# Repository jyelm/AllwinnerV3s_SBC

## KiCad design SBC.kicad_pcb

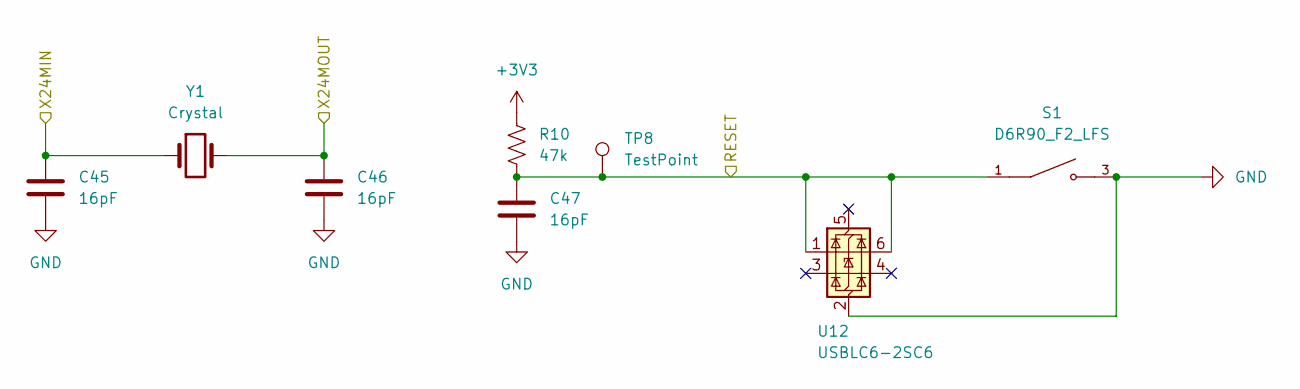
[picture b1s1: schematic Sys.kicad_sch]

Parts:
C45, C46, C47: 16pF; C_0603_1608Metric_Pad1.08x0.95mm_HandSolder
R10: 47k; R_0805_2012Metric_Pad1.20x1.40mm_HandSolder
S1: D6R90_F2_LFS; SW_D6R90_F2_LFS; PARTREV 21 Feb 22
TP8: TestPoint; TestPoint_Pad_D1.0mm
U12: USBLC6-2SC6; SOT-23-6
Y1: Crystal; Crystal_SMD_HC49-SD_HandSoldering

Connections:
+3V3: R10.1; also elsewhere on the board
/Allwinner V3S/RESET: C47.1, R10.2, S1.1, S1.2, TP8.1 (1_1), U12.1 (I/O1), U12.6 (I/O1); also elsewhere on the board
/Allwinner V3S/X24MIN: C45.1, Y1.1; also elsewhere on the board
/Allwinner V3S/X24MOUT: C46.1, Y1.2; also elsewhere on the board
GND: C45.2, C46.2, C47.2, S1.3, S1.4, U12.2 (GND); also elsewhere on the board

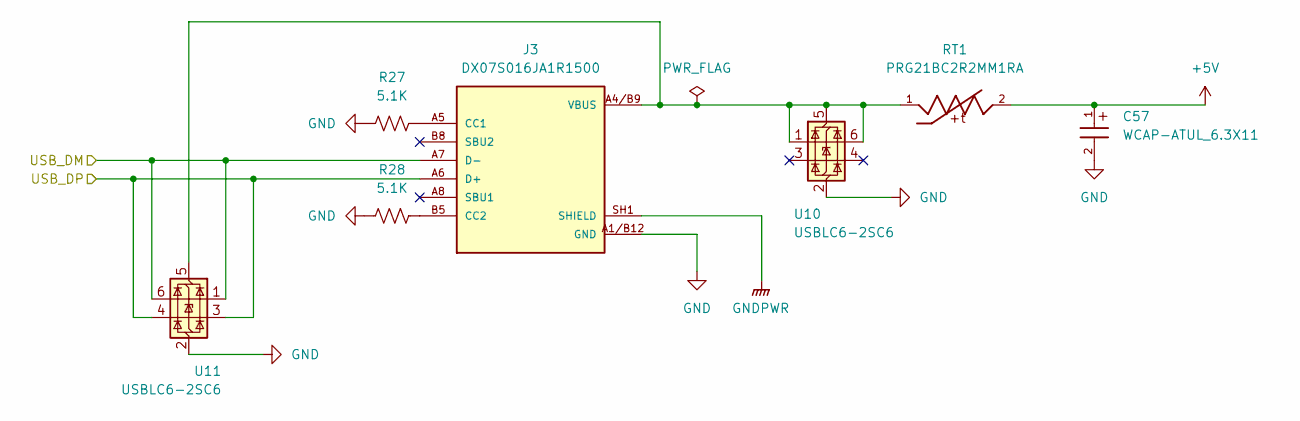
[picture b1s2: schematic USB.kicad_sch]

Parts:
C57: WCAP-ATUL_6.3X11; WCAP-ATUL_6.3X11_DXL_
J3: DX07S016JA1R1500; JAE_DX07S016JA1R1500; PARTREV 3
R27, R28: 5.1K; R_0805_2012Metric_Pad1.20x1.40mm_HandSolder
RT1: PRG21BC2R2MM1RA; THRMC2012X110N; PARTREV N/A
U10, U11: USBLC6-2SC6; SOT-23-6

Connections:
+5V: C57.1, RT1.2; also elsewhere on the board
/Allwinner V3S/USB_DM: J3.A7 (D-), J3.B7 (D-), U11.1 (I/O1), U11.6 (I/O1); also elsewhere on the board
/Allwinner V3S/USB_DP: J3.A6 (D+), J3.B6 (D+), U11.3 (I/O2), U11.4 (I/O2); also elsewhere on the board
GND: C57.2, J3.A1/B12 (GND), J3.A12/B1 (GND), R27.1, R28.1, U10.2 (GND), U11.2 (GND); also elsewhere on the board
GNDPWR: J3.SH1 (SHIELD), J3.SH2 (SHIELD), J3.SH3 (SHIELD), J3.SH4 (SHIELD), J3.SH5 (SHIELD), J3.SH6 (SHIELD); also elsewhere on the board
unnamed: J3.A5 (CC1), R27.2
unnamed: J3.B5 (CC2), R28.2
VBUS: J3.A4/B9 (VBUS), J3.B4/A9 (VBUS), RT1.1, U10.1 (I/O1), U10.5 (VBUS), U10.6 (I/O1), U11.5 (VBUS)

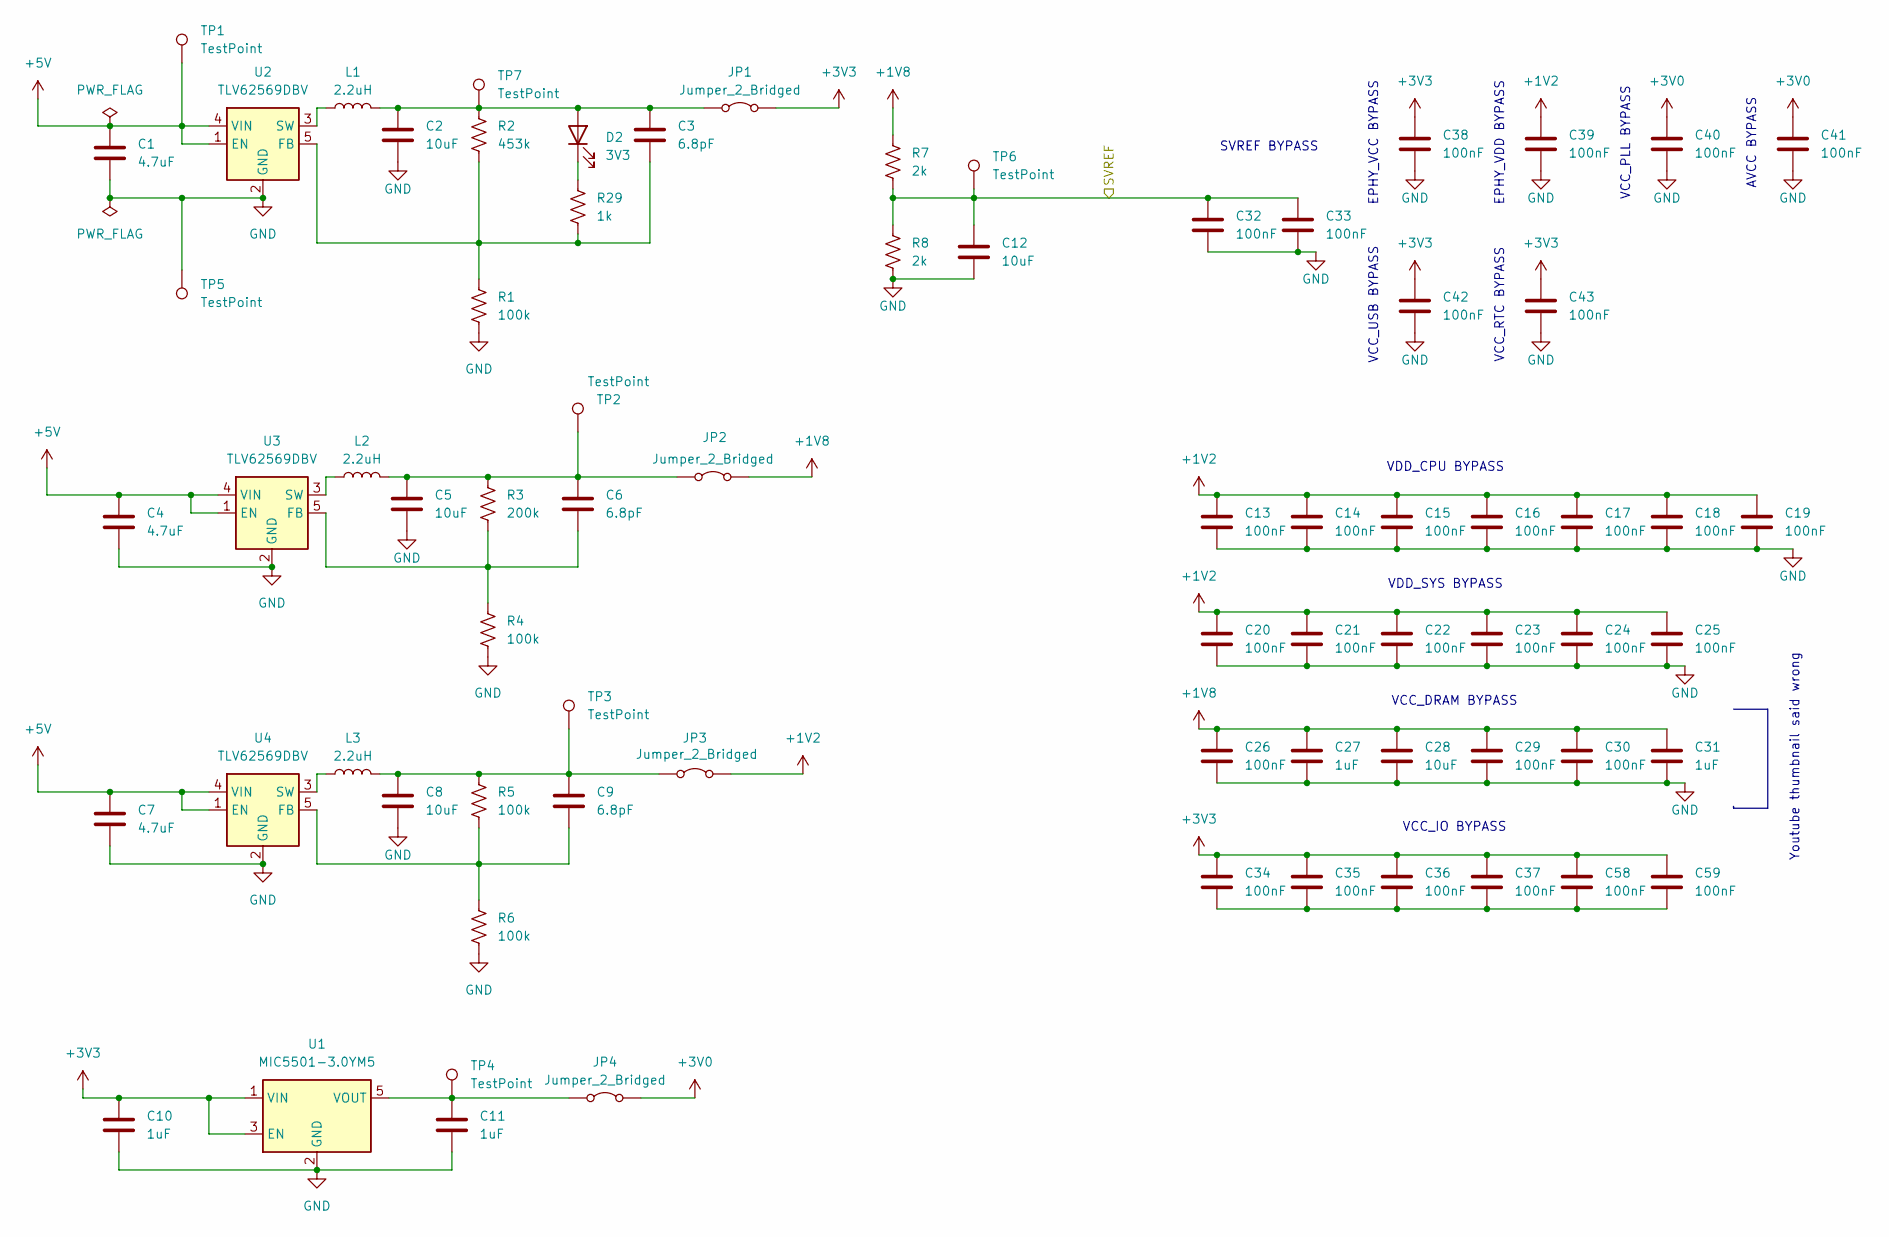
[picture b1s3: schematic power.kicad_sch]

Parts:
C1, C4, C7: 4.7uF; C_0603_1608Metric_Pad1.08x0.95mm_HandSolder
C2, C5, C8, C12, C28: 10uF; C_0603_1608Metric_Pad1.08x0.95mm_HandSolder
C3, C6, C9: 6.8pF; C_0603_1608Metric_Pad1.08x0.95mm_HandSolder
C10, C11, C27, C31: 1uF; C_0603_1608Metric_Pad1.08x0.95mm_HandSolder
C13, C14, C15, C16, C17, C18, C19, C20, C21, C22, C23, C24, C25, C26, C29, C30, C32, C33, C34, C35, C36, C37, C38, C39, C40, C41, C42, C43, C58, C59: 100nF; C_0603_1608Metric_Pad1.08x0.95mm_HandSolder
D2: 3V3; LED_0805_2012Metric_Pad1.15x1.40mm_HandSolder
JP1, JP2, JP3, JP4: Jumper_2_Bridged; Jumper_Harwin_S1621_P10.9mm
L1, L2, L3: 2.2uH; R_0805_2012Metric_Pad1.20x1.40mm_HandSolder
R1, R4, R5, R6: 100k; R_0805_2012Metric_Pad1.20x1.40mm_HandSolder
R2: 453k; R_0805_2012Metric_Pad1.20x1.40mm_HandSolder
R3: 200k; R_0805_2012Metric_Pad1.20x1.40mm_HandSolder
R7, R8: 2k; R_0805_2012Metric_Pad1.20x1.40mm_HandSolder
R29: 1k; R_0805_2012Metric_Pad1.20x1.40mm_HandSolder
TP1, TP2, TP3, TP4, TP5, TP6, TP7: TestPoint; TestPoint_Pad_D1.0mm
U1: MIC5501-3.0YM5; SOT-23-5
U2, U3, U4: TLV62569DBV; SOT-23-5

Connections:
+1V2: C13.1, C14.1, C15.1, C16.1, C17.1, C18.1, C19.1, C20.1, C21.1, C22.1, C23.1, C24.1, C25.1, C39.1, JP3.2 (B); also elsewhere on the board
+1V8: C26.1, C27.1, C28.1, C29.1, C30.1, C31.1, JP2.2 (B), R7.1; also elsewhere on the board
+3V0: C40.1, C41.1, JP4.2 (B); also elsewhere on the board
+3V3: C10.1, C34.1, C35.1, C36.1, C37.1, C38.1, C42.1, C43.1, C58.1, C59.1, JP1.2 (B), U1.1 (VIN), U1.3 (EN); also elsewhere on the board
+5V: C1.1, C4.1, C7.1, TP1.1 (1_1), U2.1 (EN), U2.4 (VIN), U3.1 (EN), U3.4 (VIN), U4.1 (EN), U4.4 (VIN); also elsewhere on the board
/Allwinner V3S/SVREF: C12.1, C32.1, C33.1, R7.2, R8.1, TP6.1 (1_1); also elsewhere on the board
GND: C1.2, C2.2, C4.2, C5.2, C7.2, C8.2, C10.2, C11.2, C12.2, C13.2, C14.2, C15.2, C16.2, C17.2, C18.2, C19.2, C20.2, C21.2, C22.2, C23.2, C24.2, C25.2, C26.2, C27.2, C28.2, C29.2, C30.2, C31.2, C32.2, C33.2, C38.2, C39.2, C40.2, C41.2, C42.2, C43.2, R1.2, R4.2, R6.2, R8.2, TP5.1 (1_1), U1.2 (GND), U2.2 (GND), U3.2 (GND), U4.2 (GND); also elsewhere on the board
unnamed: C34.2, C35.2, C36.2, C37.2, C58.2, C59.2
unnamed: C2.1, C3.1, D2.2 (A), JP1.1 (A), L1.2, R2.1, TP7.1 (1_1)
unnamed: D2.1 (K), R29.1
unnamed: C5.1, C6.1, JP2.1 (A), L2.2, R3.1, TP2.1 (1_1)
unnamed: C8.1, C9.1, JP3.1 (A), L3.2, R5.1, TP3.1 (1_1)
unnamed: C11.1, JP4.1 (A), TP4.1 (1_1), U1.5 (VOUT)
unnamed: C3.2, R1.1, R2.2, R29.2, U2.5 (FB)
unnamed: L1.1, U2.3 (SW)
unnamed: C6.2, R3.2, R4.1, U3.5 (FB)
unnamed: L2.1, U3.3 (SW)
unnamed: C9.2, R5.2, R6.1, U4.5 (FB)
unnamed: L3.1, U4.3 (SW)

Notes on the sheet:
VCC_IO BYPASS
VCC_PLL BYPASS
VCC_DRAM BYPASS
AVCC BYPASS
SVREF BYPASS
VDD_SYS BYPASS
VCC_RTC BYPASS
EPHY_VCC BYPASS
VDD_CPU BYPASS
VCC_USB BYPASS
EPHY_VDD BYPASS
Youtube thumbnail said wrong

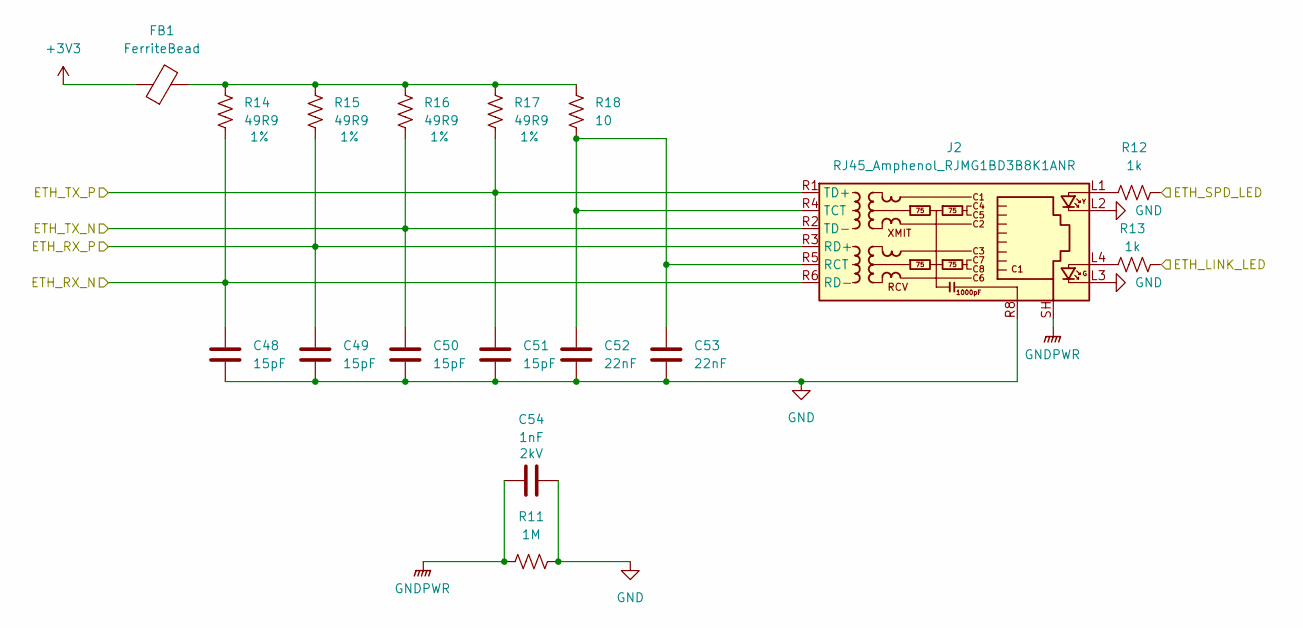
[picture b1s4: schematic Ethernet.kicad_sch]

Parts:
C48, C49, C50, C51: 15pF; C_0603_1608Metric_Pad1.08x0.95mm_HandSolder
C52, C53: 22nF; C_0603_1608Metric_Pad1.08x0.95mm_HandSolder
C54: 1nF; C_0603_1608Metric_Pad1.08x0.95mm_HandSolder; Voltage Rating 2kV
FB1: FerriteBead; L_0805_2012Metric_Pad1.05x1.20mm_HandSolder
J2: RJ45_Amphenol_RJMG1BD3B8K1ANR
R11: 1M; R_0805_2012Metric_Pad1.20x1.40mm_HandSolder
R12, R13: 1k; R_0805_2012Metric_Pad1.20x1.40mm_HandSolder
R14, R15, R16, R17: 49R9; R_0805_2012Metric_Pad1.20x1.40mm_HandSolder; Tolerance 1%
R18: 10; R_0805_2012Metric_Pad1.20x1.40mm_HandSolder

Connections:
+3V3: FB1.1; also elsewhere on the board
/Allwinner V3S/ETH_LINK_LED: R13.2; also elsewhere on the board
/Allwinner V3S/ETH_RX_N: C48.1, J2.R6 (RD-), R14.1; also elsewhere on the board
/Allwinner V3S/ETH_RX_P: C49.1, J2.R3 (RD+), R15.1; also elsewhere on the board
/Allwinner V3S/ETH_SPD_LED: R12.2; also elsewhere on the board
/Allwinner V3S/ETH_TX_N: C50.1, J2.R2 (TD-), R16.1; also elsewhere on the board
/Allwinner V3S/ETH_TX_P: C51.1, J2.R1 (TD+), R17.1; also elsewhere on the board
GND: C48.2, C49.2, C50.2, C51.2, C52.2, C53.2, C54.2, J2.L2, J2.L3, J2.R8, R11.2; also elsewhere on the board
GNDPWR: C54.1, J2.SH, R11.1; also elsewhere on the board
unnamed: FB1.2, R14.2, R15.2, R16.2, R17.2, R18.2
unnamed: J2.L1, R12.1
unnamed: J2.L4, R13.1
unnamed: C52.1, C53.1, J2.R4 (TCT), J2.R5 (RCT), R18.1

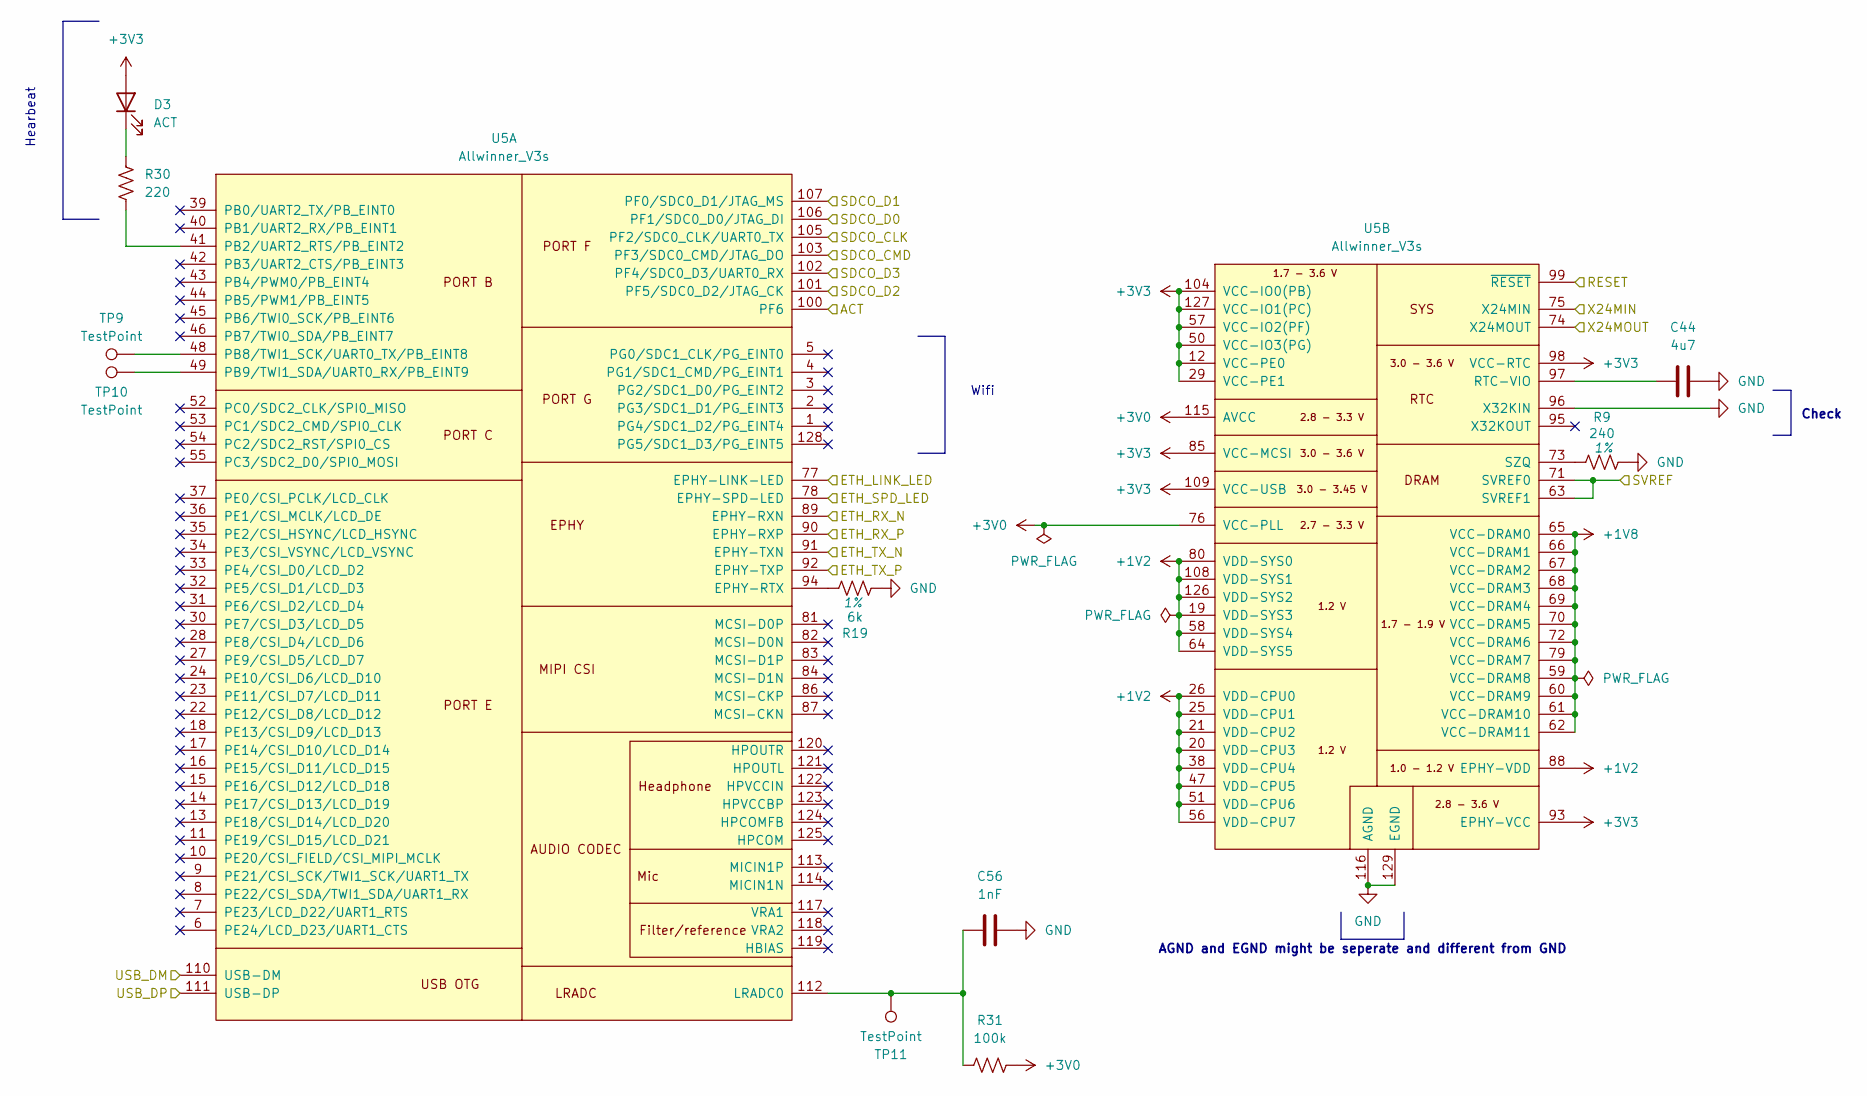
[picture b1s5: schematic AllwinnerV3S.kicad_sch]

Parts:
C44: 4u7; C_0603_1608Metric_Pad1.08x0.95mm_HandSolder
C56: 1nF; C_0603_1608Metric_Pad1.08x0.95mm_HandSolder
D3: ACT; LED_0805_2012Metric_Pad1.15x1.40mm_HandSolder
R9: 240; R_0805_2012Metric_Pad1.20x1.40mm_HandSolder; Tolerance 1%
R19: 6k; R_0805_2012Metric_Pad1.20x1.40mm_HandSolder; Tolerance 1%
R30: 220; R_0805_2012Metric_Pad1.20x1.40mm_HandSolder
R31: 100k; R_0805_2012Metric_Pad1.20x1.40mm_HandSolder
TP9, TP10, TP11: TestPoint; TestPoint_Pad_D1.0mm
U5: Allwinner_V3s; eLQFP-128_14x14_Pitch0.4mm_EPAD_6.60mm

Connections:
+1V2: U5.19 (VDD-SYS3), U5.20 (VDD-CPU3), U5.21 (VDD-CPU2), U5.25 (VDD-CPU1), U5.26 (VDD-CPU0), U5.38 (VDD-CPU4), U5.47 (VDD-CPU5), U5.51 (VDD-CPU6), U5.56 (VDD-CPU7), U5.58 (VDD-SYS4), U5.64 (VDD-SYS5), U5.80 (VDD-SYS0), U5.88 (EPHY-VDD), U5.108 (VDD-SYS1), U5.126 (VDD-SYS2); also elsewhere on the board
+1V8: U5.59 (VCC-DRAM8), U5.60 (VCC-DRAM9), U5.61 (VCC-DRAM10), U5.62 (VCC-DRAM11), U5.65 (VCC-DRAM0), U5.66 (VCC-DRAM1), U5.67 (VCC-DRAM2), U5.68 (VCC-DRAM3), U5.69 (VCC-DRAM4), U5.70 (VCC-DRAM5), U5.72 (VCC-DRAM6), U5.79 (VCC-DRAM7); also elsewhere on the board
+3V0: R31.2, U5.76 (VCC-PLL), U5.115 (AVCC); also elsewhere on the board
+3V3: D3.2 (A), U5.12 (VCC-PE0), U5.29 (VCC-PE1), U5.50 (VCC-IO3(PG)), U5.57 (VCC-IO2(PF)), U5.85 (VCC-MCSI), U5.93 (EPHY-VCC), U5.98 (VCC-RTC), U5.104 (VCC-IO0(PB)), U5.109 (VCC-USB), U5.127 (VCC-IO1(PC)); also elsewhere on the board
/Allwinner V3S/ACT: U5.100 (PF6); also elsewhere on the board
/Allwinner V3S/ETH_LINK_LED: U5.77 (EPHY-LINK-LED); also elsewhere on the board
/Allwinner V3S/ETH_RX_N: U5.89 (EPHY-RXN); also elsewhere on the board
/Allwinner V3S/ETH_RX_P: U5.90 (EPHY-RXP); also elsewhere on the board
/Allwinner V3S/ETH_SPD_LED: U5.78 (EPHY-SPD-LED); also elsewhere on the board
/Allwinner V3S/ETH_TX_N: U5.91 (EPHY-TXN); also elsewhere on the board
/Allwinner V3S/ETH_TX_P: U5.92 (EPHY-TXP); also elsewhere on the board
/Allwinner V3S/RESET: U5.99 (~RESET); also elsewhere on the board
/Allwinner V3S/SDCO_CLK: U5.105 (PF2/SDC0_CLK/UART0_TX); also elsewhere on the board
/Allwinner V3S/SDCO_CMD: U5.103 (PF3/SDC0_CMD/JTAG_DO); also elsewhere on the board
/Allwinner V3S/SDCO_D0: U5.106 (PF1/SDC0_D0/JTAG_DI); also elsewhere on the board
/Allwinner V3S/SDCO_D1: U5.107 (PF0/SDC0_D1/JTAG_MS); also elsewhere on the board
/Allwinner V3S/SDCO_D2: U5.101 (PF5/SDC0_D2/JTAG_CK); also elsewhere on the board
/Allwinner V3S/SDCO_D3: U5.102 (PF4/SDC0_D3/UART0_RX); also elsewhere on the board
/Allwinner V3S/SVREF: U5.63 (SVREF1), U5.71 (SVREF0); also elsewhere on the board
/Allwinner V3S/USB_DM: U5.110 (USB-DM); also elsewhere on the board
/Allwinner V3S/USB_DP: U5.111 (USB-DP); also elsewhere on the board
/Allwinner V3S/X24MIN: U5.75 (X24MIN); also elsewhere on the board
/Allwinner V3S/X24MOUT: U5.74 (X24MOUT); also elsewhere on the board
GND: C44.2, C56.1, R9.2, R19.1, U5.96 (X32KIN), U5.116 (AGND), U5.129 (EGND); also elsewhere on the board
unnamed: D3.1 (K), R30.1
unnamed: R19.2, U5.94 (EPHY-RTX)
unnamed: C56.2, R31.1, TP11.1 (1_1), U5.112 (LRADC0)
unnamed: R30.2, U5.41 (PB2/UART2_RTS/PB_EINT2)
unnamed: TP9.1 (1_1), U5.48 (PB8/TWI1_SCK/UART0_TX/PB_EINT8)
unnamed: TP10.1 (1_1), U5.49 (PB9/TWI1_SDA/UART0_RX/PB_EINT9)
unnamed: C44.1, U5.97 (RTC-VIO)
unnamed: R9.1, U5.73 (SZQ)

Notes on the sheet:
Wifi
AGND and EGND might be seperate and different from GND
Hearbeat
Check

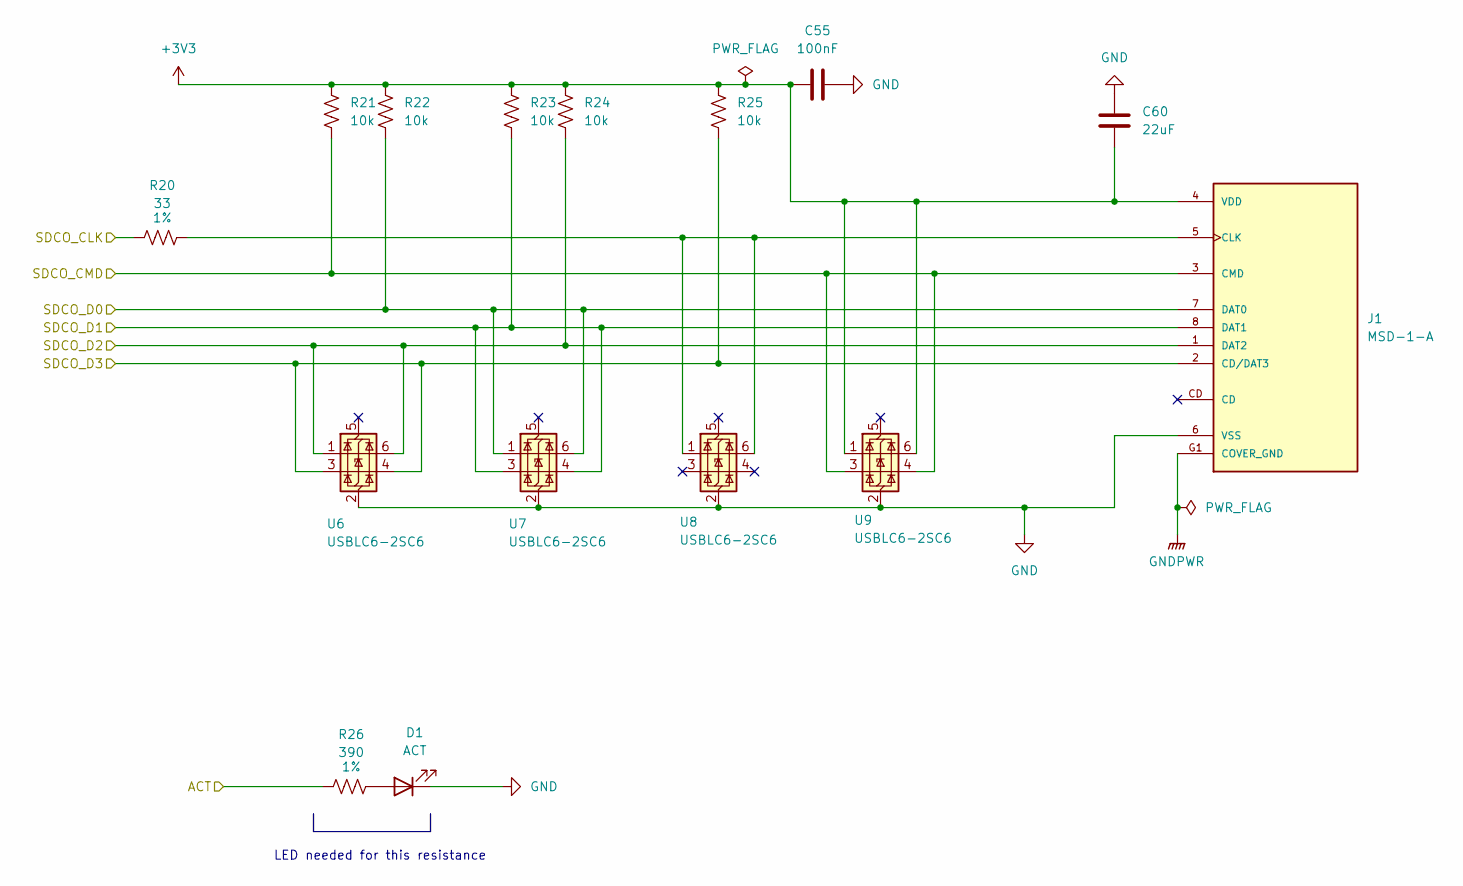
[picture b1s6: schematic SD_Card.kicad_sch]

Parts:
C55: 100nF; C_0603_1608Metric_Pad1.08x0.95mm_HandSolder
C60: 22uF; C_0603_1608Metric_Pad1.08x0.95mm_HandSolder
D1: ACT; LED_0805_2012Metric_Pad1.15x1.40mm_HandSolder
J1: MSD-1-A; CUI_MSD-1-A; PARTREV 1.0
R20: 33; R_0805_2012Metric_Pad1.20x1.40mm_HandSolder; Tolerance 1%
R21, R22, R23, R24, R25: 10k; R_0805_2012Metric_Pad1.20x1.40mm_HandSolder
R26: 390; R_0805_2012Metric_Pad1.20x1.40mm_HandSolder; Tolerance 1%
U6, U7, U8, U9: USBLC6-2SC6; SOT-23-6

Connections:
+3V3: C55.1, C60.1, J1.4 (VDD), R21.1, R22.1, R23.1, R24.1, R25.1, U9.1 (I/O1), U9.6 (I/O1); also elsewhere on the board
/Allwinner V3S/ACT: R26.1; also elsewhere on the board
/Allwinner V3S/SDCO_CLK: R20.1; also elsewhere on the board
/Allwinner V3S/SDCO_CMD: J1.3 (CMD), R21.2, U9.3 (I/O2), U9.4 (I/O2); also elsewhere on the board
/Allwinner V3S/SDCO_D0: J1.7 (DAT0), R22.2, U7.1 (I/O1), U7.6 (I/O1); also elsewhere on the board
/Allwinner V3S/SDCO_D1: J1.8 (DAT1), R23.2, U7.3 (I/O2), U7.4 (I/O2); also elsewhere on the board
/Allwinner V3S/SDCO_D2: J1.1 (DAT2), R24.2, U6.1 (I/O1), U6.6 (I/O1); also elsewhere on the board
/Allwinner V3S/SDCO_D3: J1.2 (CD/DAT3), R25.2, U6.3 (I/O2), U6.4 (I/O2); also elsewhere on the board
GND: C55.2, C60.2, D1.1 (K), J1.6 (VSS), U6.2 (GND), U7.2 (GND), U8.2 (GND), U9.2 (GND); also elsewhere on the board
GNDPWR: J1.G1 (COVER_GND), J1.G2 (COVER_GND), J1.G3 (COVER_GND), J1.G4 (COVER_GND); also elsewhere on the board
unnamed: D1.2 (A), R26.2
unnamed: J1.5 (CLK), R20.2, U8.1 (I/O1), U8.6 (I/O1)

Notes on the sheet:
LED needed for this resistance

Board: 4 copper layers, 131 parts (19 on the bottom side), 55 nets, no tracks yet.
